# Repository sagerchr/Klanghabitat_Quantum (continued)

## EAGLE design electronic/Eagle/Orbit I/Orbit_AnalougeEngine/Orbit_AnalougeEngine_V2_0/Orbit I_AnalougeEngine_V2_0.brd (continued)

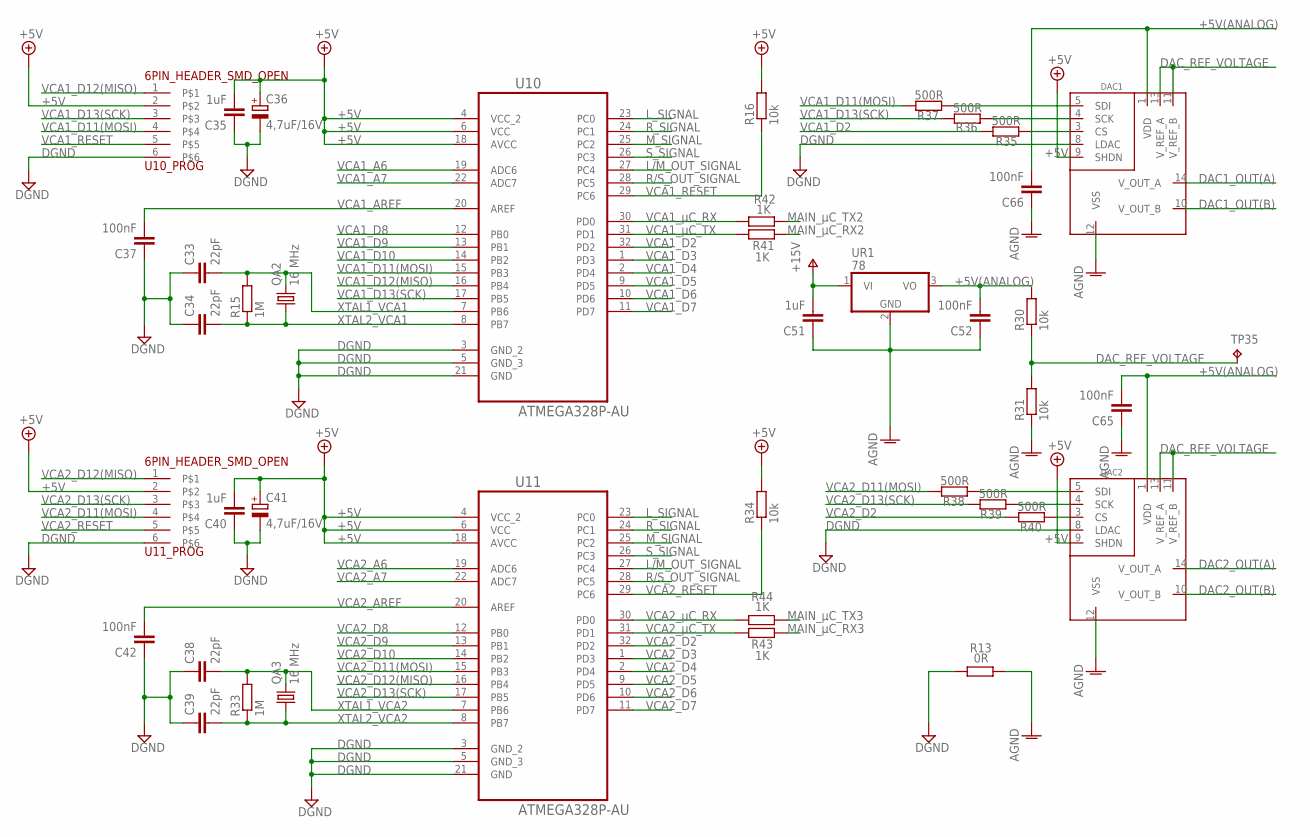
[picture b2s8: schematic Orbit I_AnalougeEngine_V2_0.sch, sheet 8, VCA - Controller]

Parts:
C33, C34, C38, C39: 22pF; C0603
C35, C40, C51: 1uF; C0603
C36, C41: 4,7uF/16V; 153CLV-0605
C37, C42, C52, C65, C66: 100nF; C0603
DAC1, DAC2: MCP4922; SOIC16
QA2, QA3: 16 MHz; SM49
R13: 0R; R0805
R15, R33: 1M; R0805
R16, R30, R31, R34: 10k; R0805
R35, R36, R37, R38, R39, R40: 500R; R0805
R41, R42, R43, R44: 1K; R0805
TP35: TPTHT; THT_PIN
U10, U11: ATMEGA328P-AU; QFP80P900X900X120-32N
U10_PROG, U11_PROG: 6PIN_HEADER_SMD_OPEN
UR1: 78; TO252

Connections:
+5V: C35.2, C36.+, C40.2, C41.+, DAC1.9 (SHDN), DAC2.9 (SHDN), R16.2, R34.2, U10.4 (VCC_2), U10.6 (VCC), U10.18 (AVCC), U10_PROG.2, U11.4 (VCC_2), U11.6 (VCC), U11.18 (AVCC), U11_PROG.2; also elsewhere on the board
+5V(ANALOG): C52.2, C65.2, C66.2, DAC1.1 (VDD), DAC2.1 (VDD), R30.2, UR1.3 (VO)
AGND: C51.1, C52.1, C65.1, C66.1, DAC1.12 (VSS), DAC2.12 (VSS), R13.2, R31.1, UR1.2 (GND); also elsewhere on the board
DAC1_OUT(A): DAC1.14 (V_OUT_A); also elsewhere on the board
DAC1_OUT(B): DAC1.10 (V_OUT_B); also elsewhere on the board
DAC2_OUT(A): DAC2.14 (V_OUT_A); also elsewhere on the board
DAC2_OUT(B): DAC2.10 (V_OUT_B); also elsewhere on the board
DAC_REF_VOLTAGE: DAC1.11 (V_REF_B), DAC1.13 (V_REF_A), DAC2.11 (V_REF_B), DAC2.13 (V_REF_A), R30.1, R31.2, TP35.P$1
DGND: C33.1, C34.1, C35.1, C36.-, C37.1, C38.1, C39.1, C40.1, C41.-, C42.1, DAC1.8 (LDAC), DAC2.8 (LDAC), R13.1, U10.3 (GND_2), U10.5 (GND_3), U10.21 (GND), U10_PROG.6, U11.3 (GND_2), U11.5 (GND_3), U11.21 (GND), U11_PROG.6; also elsewhere on the board
L/M_OUT_SIGNAL: U10.27 (PC4), U11.27 (PC4); also elsewhere on the board
L_SIGNAL: U10.23 (PC0), U11.23 (PC0); also elsewhere on the board
MAIN_µC_RX2: R41.2; also elsewhere on the board
MAIN_µC_RX3: R43.2; also elsewhere on the board
MAIN_µC_TX2: R42.2; also elsewhere on the board
MAIN_µC_TX3: R44.2; also elsewhere on the board
M_SIGNAL: U10.25 (PC2), U11.25 (PC2); also elsewhere on the board
unnamed: DAC1.3 (CS), R35.2
unnamed: DAC1.4 (SCK), R36.2
unnamed: DAC1.5 (SDI), R37.2
unnamed: DAC2.3 (CS), R40.2
unnamed: DAC2.4 (SCK), R39.2
unnamed: DAC2.5 (SDI), R38.2
R/S_OUT_SIGNAL: U10.28 (PC5), U11.28 (PC5); also elsewhere on the board
R_SIGNAL: U10.24 (PC1), U11.24 (PC1); also elsewhere on the board
S_SIGNAL: U10.26 (PC3), U11.26 (PC3); also elsewhere on the board
V+: C51.2, UR1.1 (VI); also elsewhere on the board
VCA1_A6: U10.19 (ADC6)
VCA1_A7: U10.22 (ADC7)
VCA1_AREF: C37.2, U10.20 (AREF)
VCA1_D2: R35.1, U10.32 (PD2)
VCA1_D3: U10.1 (PD3)
VCA1_D4: U10.2 (PD4)
VCA1_D5: U10.9 (PD5)
VCA1_D6: U10.10 (PD6)
VCA1_D7: U10.11 (PD7)
VCA1_D8: U10.12 (PB0)
VCA1_D9: U10.13 (PB1)
VCA1_D10: U10.14 (PB2)
VCA1_D11(MOSI): R37.1, U10.15 (PB3), U10_PROG.4
VCA1_D12(MISO): U10.16 (PB4), U10_PROG.1
VCA1_D13(SCK): R36.1, U10.17 (PB5), U10_PROG.3
VCA1_RESET: R16.1, U10.29 (PC6), U10_PROG.5
VCA1_µC_RX: R42.1, U10.30 (PD0)
VCA1_µC_TX: R41.1, U10.31 (PD1)
VCA2_A6: U11.19 (ADC6)
VCA2_A7: U11.22 (ADC7)
VCA2_AREF: C42.2, U11.20 (AREF)
VCA2_D2: R40.1, U11.32 (PD2)
VCA2_D3: U11.1 (PD3)
VCA2_D4: U11.2 (PD4)
VCA2_D5: U11.9 (PD5)
VCA2_D6: U11.10 (PD6)
VCA2_D7: U11.11 (PD7)
VCA2_D8: U11.12 (PB0)
VCA2_D9: U11.13 (PB1)
VCA2_D10: U11.14 (PB2)
VCA2_D11(MOSI): R38.1, U11.15 (PB3), U11_PROG.4
VCA2_D12(MISO): U11.16 (PB4), U11_PROG.1
VCA2_D13(SCK): R39.1, U11.17 (PB5), U11_PROG.3
VCA2_RESET: R34.1, U11.29 (PC6), U11_PROG.5
VCA2_µC_RX: R44.1, U11.30 (PD0)
VCA2_µC_TX: R43.1, U11.31 (PD1)
XTAL1_VCA1: C33.2, QA2.2, R15.2, U10.7 (PB6)
XTAL1_VCA2: C38.2, QA3.2, R33.2, U11.7 (PB6)
XTAL2_VCA1: C34.2, QA2.1, R15.1, U10.8 (PB7)
XTAL2_VCA2: C39.2, QA3.1, R33.1, U11.8 (PB7)

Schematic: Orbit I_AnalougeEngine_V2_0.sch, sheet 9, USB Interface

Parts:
C19, C32, C43: 100nF; C0603
C23, C24: 22pF; C0603
C31: 1uF; C0603
D1: Shotky-CD1206; SOD323-R
F1: FUSE_500 mA; RESETABLE-FUSE
Q1: BLM21; RESC2012X85
QA1: 16 MHz; SM49
R1, R2: 22R; R0805
R3, R4: 1M; R0805
R5, R6, R45: 1k; R0805
U5: ATMEGA16U2-AU; QFP80P900X900X120-32N
U5_PROG: 6PIN_HEADER_SMD_OPEN
USB1: SMARTPRJ_PN61729
V1, V2: CG0603ML; VARC2513X70

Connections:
+5V: C19.1, D1.C, R4.2, U5.4 (VCC), U5.32 (AVCC), U5_PROG.2; also elsewhere on the board
C_D(+): R2.1, USB1.3, V2.1
C_D(-): R1.1, USB1.2, V1.1
C_UVCC: F1.1, USB1.1
D(+): R2.2, U5.29 (D+)
D(-): R1.2, U5.30 (D-)
DGND: C19.2, C23.1, C24.1, C32.2, R45.1, U5.3 (GND), U5_PROG.6; also elsewhere on the board
MAIN_µC_RESET: C43.1; also elsewhere on the board
MAIN_µC_RX0: R5.2; also elsewhere on the board
MAIN_µC_TX0: R6.2; also elsewhere on the board
unnamed: Q1.1, USB1.P$1, USB1.P$2, V1.2, V2.2
unnamed: C43.2, R45.2, U5.13 (/_HWB_/_AIN6_/_T0_/_INT7)_PD7)
UCAP: C31.2, U5.27 (UCAP)
USB_µC_MISO: U5.17 (PB3_(PDO_/_MISO_/_PCINT3)), U5_PROG.1
USB_µC_MOSI: U5.16 ((PDI_/_MOSI_/_PCINT2)_PB2), U5_PROG.4
USB_µC_RESET: D1.A, R4.1, U5.24 (~RESET_(PC1_/_DW)), U5_PROG.5
USB_µC_RX: R6.1, U5.8 ((RXD1_/_AIN1_/_INT2)_PD2)
USB_µC_SCK: U5.15 ((SCLK_/_PCINT1)_PB1), U5_PROG.3
USB_µC_TX: R5.1, U5.9 ((TXD1_/_INT3)_PD3)
USB_µC_UGND: C31.1, Q1.2, U5.28 (UGND), USB1.4
USB_µC_XTAL1: C24.2, QA1.2, R3.2, U5.1 (XTAL1)
USB_µC_XTAL2: C23.2, QA1.1, R3.1, U5.2 ((PC0)_XTAL2)
UVCC: C32.1, F1.2, U5.31 (UVCC)

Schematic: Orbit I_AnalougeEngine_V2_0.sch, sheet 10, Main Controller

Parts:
C20, C47, C48, C49, C50: 100nF; C0603
C44, C45, C46: 22pF; C0603
CONN1: 10PIN_HEADER_SMD; 87832-10
D2: Shotky-CD1206; SOD323-R
QA4: 16 MHz; SM49
R32, R68: 1k; R0805
R46, R47: 1M; R0805
TP27, TP28, TP29, TP30, TP31, TP32, TP33, TP34: TPTHT; THT_PIN
U1: ATMEGA2560-16AU; QFP50P1600X1600X120-100N
U1_PROG: MAIN_µC; 6PIN_HEADER_SMD_OPEN

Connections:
+5V: C20.1, C47.1, C48.1, C49.1, CONN1.1, CONN1.2, CONN1.3, D2.C, R46.2, U1.10 (VCC_3), U1.31 (VCC_2), U1.61 (VCC_4), U1.80 (VCC), U1.100 (AVCC), U1_PROG.2; also elsewhere on the board
DGND: C20.2, C44.1, C45.1, C46.2, C47.2, C48.2, C49.2, C50.2, CONN1.5, CONN1.6, CONN1.7, CONN1.8, CONN1.10, U1.11 (GND_2), U1.32 (GND_4), U1.62 (GND_3), U1.81 (GND_5), U1.99 (GND), U1_PROG.6; also elsewhere on the board
L/M_OUT_SIGNAL: U1.93 (PF4_(ADC4/TCK)); also elsewhere on the board
L_SIGNAL: U1.97 (PF0_(ADC0)); also elsewhere on the board
MAIN_µC_AREF: C50.1, U1.98 (AREF)
MAIN_µC_D2: U1.6 ((OC3B/INT4)_PE4); also elsewhere on the board
MAIN_µC_D3: U1.7 ((OC3C/INT5)_PE5); also elsewhere on the board
MAIN_µC_D4: U1.1 ((OC0B)_PG5); also elsewhere on the board
MAIN_µC_D5: U1.5 ((OC3A/AIN1)_PE3); also elsewhere on the board
MAIN_µC_D6: U1.15 ((OC4A)_PH3); also elsewhere on the board
MAIN_µC_D7: U1.16 ((OC4B)_PH4); also elsewhere on the board
MAIN_µC_PB1(SCK): U1.20 ((SCK/PCINT1)_PB1), U1_PROG.3
MAIN_µC_PB2(MOSI): U1.21 ((MOSI/PCINT2)_PB2), U1_PROG.4
MAIN_µC_PB3(MISO): U1.22 ((MISO/PCINT3)_PB3), U1_PROG.1
MAIN_µC_RESET: C46.1, D2.A, R46.1, U1.30 (~RESET), U1_PROG.5; also elsewhere on the board
MAIN_µC_RX0: TP31.P$1, U1.2 ((RXD0/PCINT8)_PE0); also elsewhere on the board
MAIN_µC_RX1: R68.2, U1.45 ((RXD1/INT2)_PD2)
MAIN_µC_RX2: TP27.P$1, U1.12 ((RXD2)_PH0); also elsewhere on the board
MAIN_µC_RX3: TP33.P$1, U1.63 (PJ0_(RXD3/PCINT9)); also elsewhere on the board
MAIN_µC_TX0: TP32.P$1, U1.3 ((TXD0)_PE1); also elsewhere on the board
MAIN_µC_TX1: R32.2, U1.46 ((TXD1/INT3)_PD3)
MAIN_µC_TX2: TP28.P$1, U1.13 ((TXD2)_PH1); also elsewhere on the board
MAIN_µC_TX3: TP34.P$1, U1.64 (PJ1_(TXD3/PCINT10)); also elsewhere on the board
MAIN_µC_XTAL1: C44.2, QA4.2, R47.2, U1.34 (XTAL1)
MAIN_µC_XTAL2: C45.2, QA4.1, R47.1, U1.33 (XTAL2)
M_SIGNAL: U1.95 (PF2_(ADC2)); also elsewhere on the board
unnamed: CONN1.4, R68.1, TP29.P$1
unnamed: CONN1.9, R32.1, TP30.P$1
R/S_OUT_SIGNAL: U1.92 (PF5_(ADC5/TMS)); also elsewhere on the board
R_SIGNAL: U1.96 (PF1_(ADC1)); also elsewhere on the board
S_SIGNAL: U1.94 (PF3_(ADC3)); also elsewhere on the board
VCA1_EC+: U1.90 (PF7_(ADC7/TDI)); also elsewhere on the board
VCA2_EC+: U1.91 (PF6_(ADC6/TDO)); also elsewhere on the board

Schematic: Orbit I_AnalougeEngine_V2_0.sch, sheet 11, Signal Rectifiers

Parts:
C9, C10, C15, C16, C17, C18: 100nF; C0603
D3, D4, D5, D6, D7, D8, D9, D10, D11, D12, D13, D14: 4148; SOD323-R
IC2, IC3, IC6: OP275; SOIC8
L: 0R; R0805
L/M_OUT: 0R; R0805
M: 0R; R0805
R: 0R; R0805
R17, R18, R19, R20, R21, R22, R23, R24, R25, R26, R27, R28: 100k; R0805
R/S_OUT: 0R; R0805
S: 0R; R0805
TP01, TP02, TP03, TP04, TP05, TP06: TPTHT; THT_PIN

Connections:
AGND: C9.2, C10.2, C15.2, C16.2, C17.2, C18.2, IC2.3 (+IN), IC2.5 (+IN), IC3.3 (+IN), IC3.5 (+IN), IC6.3 (+IN), IC6.5 (+IN); also elsewhere on the board
L: R17.1; also elsewhere on the board
L/M_OUT(VCA1_OUT): R25.1; also elsewhere on the board
L/M_OUT_SIGNAL: L/M_OUT.2, TP03.P$1; also elsewhere on the board
L_SIGNAL: L.2, TP01.P$1; also elsewhere on the board
M: R21.1; also elsewhere on the board
M_SIGNAL: M.2, TP05.P$1; also elsewhere on the board
unnamed: D5.C, L.1, R18.2
unnamed: D4.A, IC2.2 (-IN), R17.2, R18.1
unnamed: D4.C, D5.A, IC2.1 (OUT)
unnamed: D6.A, IC2.6 (-IN), R19.2, R20.1
unnamed: D6.C, D7.A, IC2.7 (OUT)
unnamed: D7.C, R.1, R20.2
unnamed: D8.A, IC3.2 (-IN), R21.2, R22.1
unnamed: D8.C, D9.A, IC3.1 (OUT)
unnamed: D9.C, M.1, R22.2
unnamed: D10.A, IC3.6 (-IN), R23.2, R24.1
unnamed: D10.C, D11.A, IC3.7 (OUT)
unnamed: D11.C, R24.2, S.1
unnamed: D3.A, IC6.2 (-IN), R25.2, R26.1
unnamed: D3.C, D12.A, IC6.1 (OUT)
unnamed: D12.C, L/M_OUT.1, R26.2
unnamed: D13.A, IC6.6 (-IN), R27.2, R28.1
unnamed: D13.C, D14.A, IC6.7 (OUT)
unnamed: D14.C, R28.2, R/S_OUT.1
R: R19.1; also elsewhere on the board
R/S_OUT(VCA2_OUT): R27.1; also elsewhere on the board
R/S_OUT_SIGNAL: R/S_OUT.2, TP04.P$1; also elsewhere on the board
R_SIGNAL: R.2, TP02.P$1; also elsewhere on the board
S: R23.1; also elsewhere on the board
S_SIGNAL: S.2, TP06.P$1; also elsewhere on the board
V+: C10.1, C16.1, C18.1, IC2.8 (V+), IC3.8 (V+), IC6.8 (V+); also elsewhere on the board
V-: C9.1, C15.1, C17.1, IC2.4 (V-), IC3.4 (V-), IC6.4 (V-); also elsewhere on the board

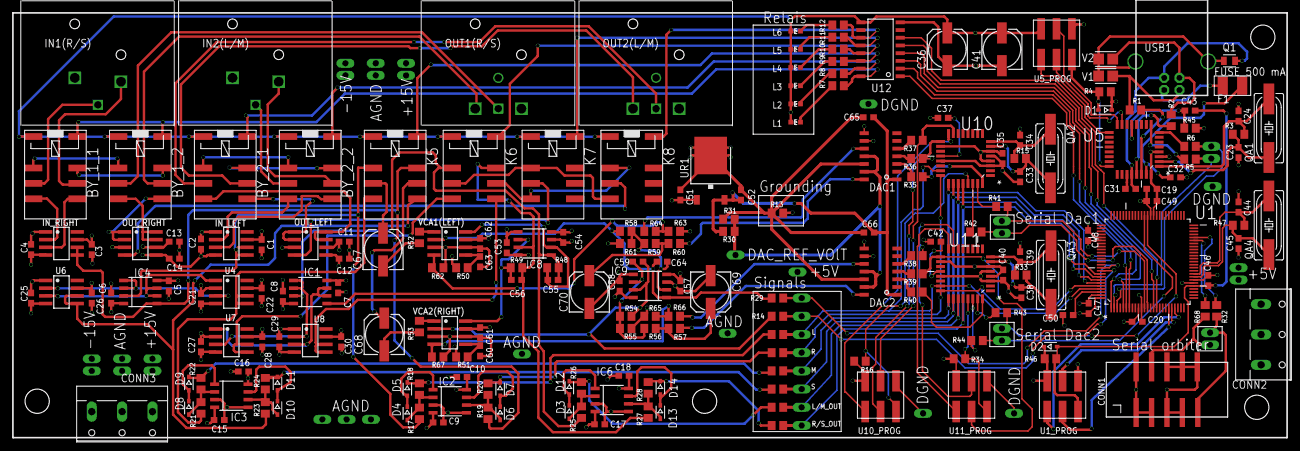
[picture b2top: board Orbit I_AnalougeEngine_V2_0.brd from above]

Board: 4 copper layers, 210.0 x 70.0 mm, 258 parts (0 on the bottom side), 170 nets.

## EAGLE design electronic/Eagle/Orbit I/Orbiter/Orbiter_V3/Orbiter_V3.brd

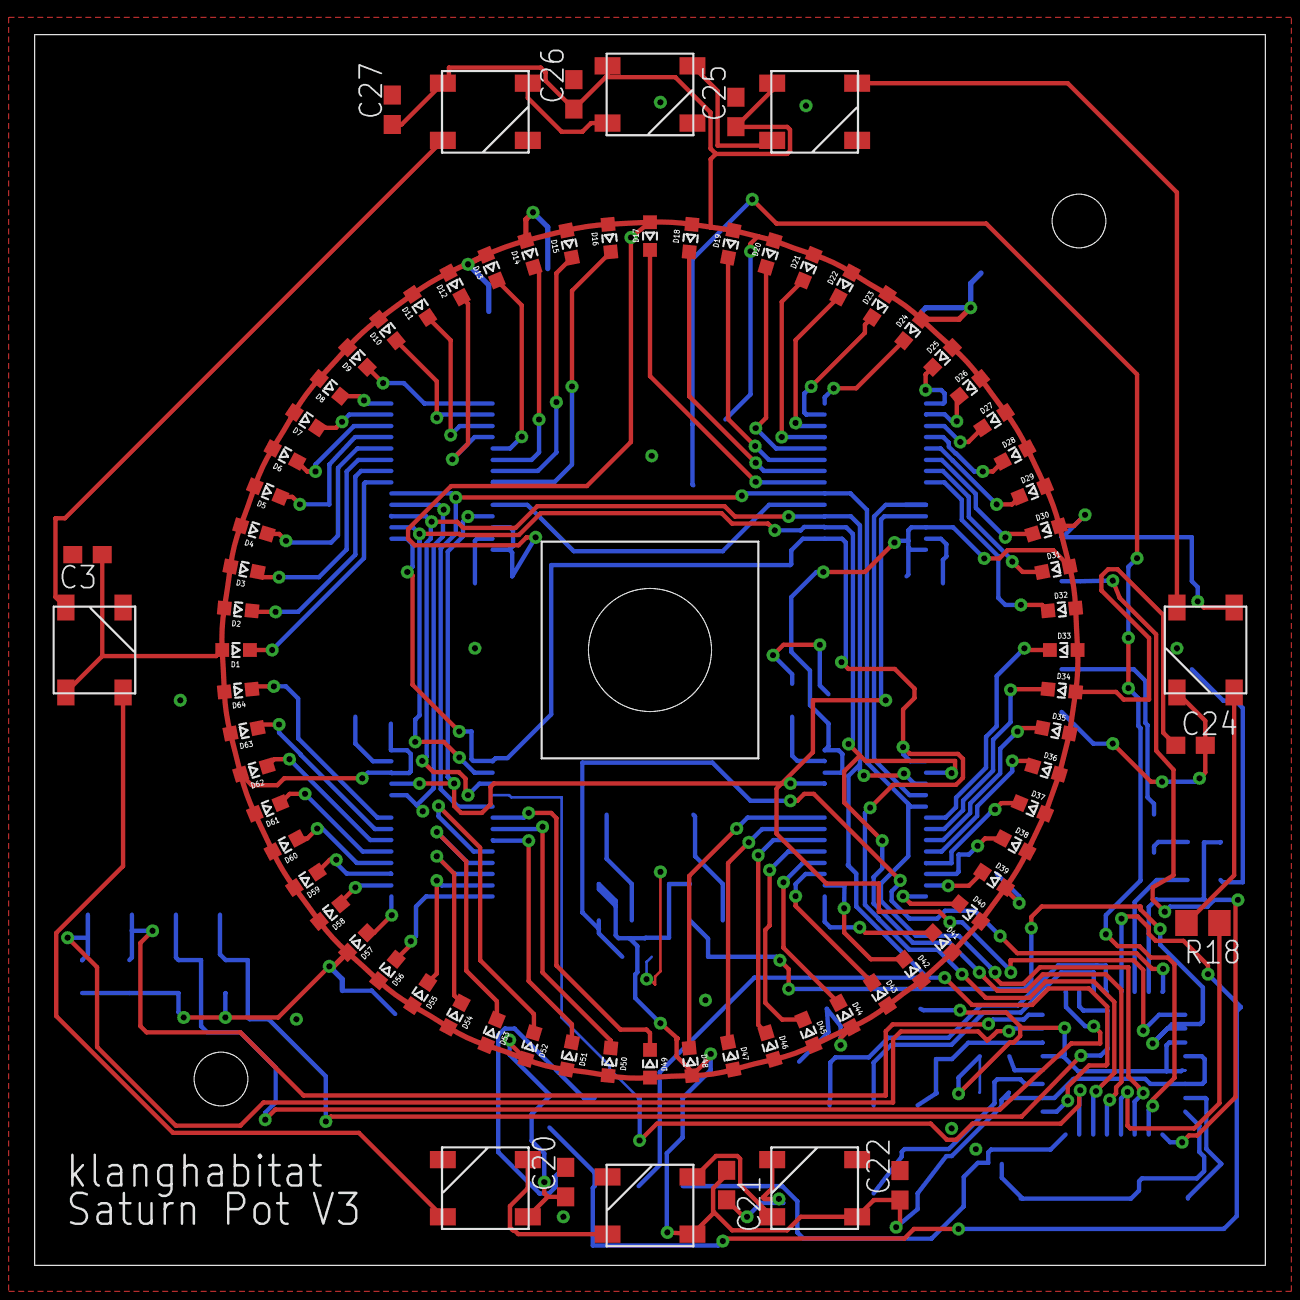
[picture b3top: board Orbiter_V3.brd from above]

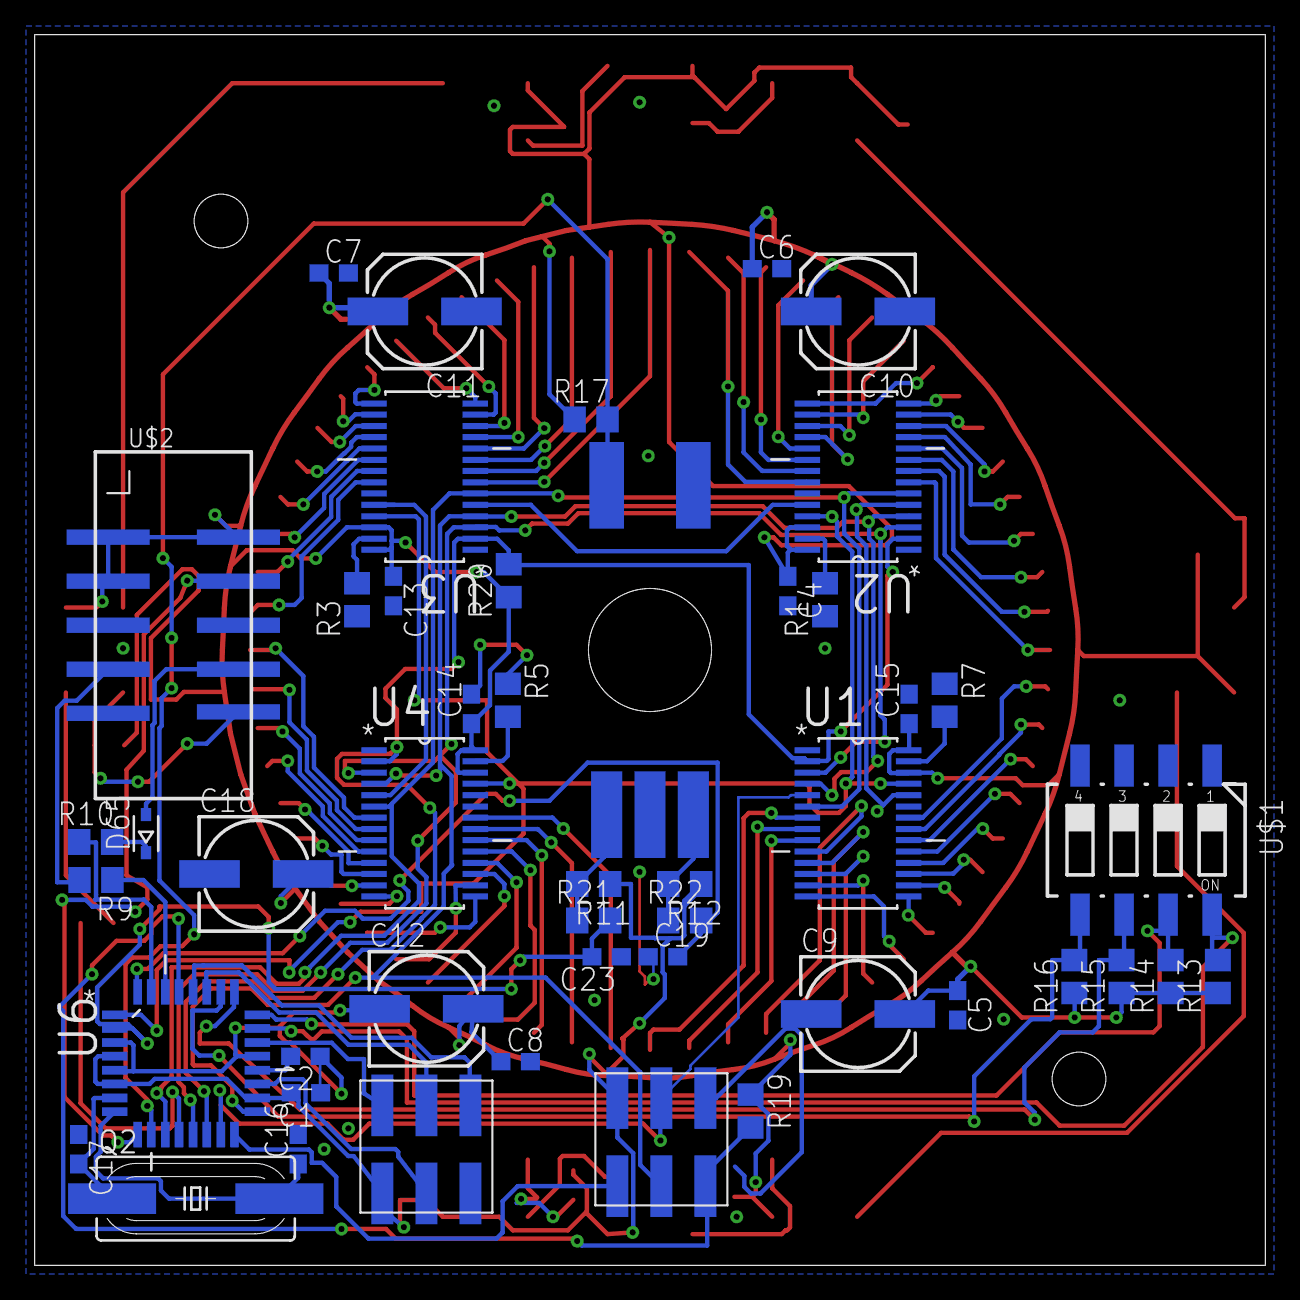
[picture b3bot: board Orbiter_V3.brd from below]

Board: 2 copper layers, 71.0 x 71.0 mm, 129 parts (47 on the bottom side), 112 nets.

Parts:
C1: 1uF; C0603
C2: 100nF; C0603
C3, C4, C5, C6, C7, C8, C13, C14, C15, C20, C21, C22, C24, C25, C26, C27: 100n; C0603
C9, C10, C11, C12: 10u; 153CLV-0605
C16, C17: 22p; C0603
C18: 4,7uF/16V; 153CLV-0605
C19, C23: 10nF; C0603
D1, D2, D3, D4, D5, D6, D7, D8, D9, D10, D11, D12, D13, D14, D15, D16, D17, D18, D19, D20, D21, D22, D23, D24, D25, D26, D27, D28, D29, D30, D31, D32, D33, D34, D35, D36, D37, D38, D39, D40, D41, D42, D43, D44, D45, D46, D47, D48, D49, D50, D51, D52, D53, D54, D55, D56, D57, D58, D59, D60, D61, D62, D63, D64: SMD_LED_0603; WL-SMCW_0603
D65: 4148; SOD323-R
Q2: 16MHZ; SM49
R1, R3, R5, R7: 2k; R0805
R9, R10, R18: 1k; R0805
R11, R12, R13, R14, R15, R16, R17, R19, R20, R21, R22: 10k; R0805
U1, U2, U3, U4: TLC5940; SOP65P640X120-29N
U6: ATMEGA328; QFP80P900X900X120-32N
U$1: 4PIN_DIP; CTS-219-04
U$2: 10PIN_HEADER_SMD; 87832-10
U$3, U$5: 6PIN_HEADER_SMD_OPEN
U$4: BOURNS_ENCODER; BOURNS_ENCODER_SMD
WS2, WS3, WS4, WS5, WS6, WS8, WS9, WS10: WS2812

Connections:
A0: R13.2, U6.23, U$1.8
A1: R14.2, U6.24, U$1.7
A2: R15.2, U6.25, U$1.6
A3: R16.2, U6.26, U$1.5
A4: U6.27, U$5.4
A5: U6.28, U$5.6
A6: U6.19, U$5.3
A7: U6.22, U$5.2
D0/RX: R9.1, U6.30
D1/TX: R10.1, U6.31
D2/TB: C19.2, R22.2, U6.32
D3/GSCLK: U1.25, U2.25, U3.25, U4.25, U6.1
D4/TA: C23.2, R21.2, U6.2
D5: U6.9, U$2.4
D6/SWITCH: R17.2, U6.10, U$4.S2
D7/MODE: U1.6, U2.6, U3.6, U4.6, U6.11
D8/WS2812: R18.1, U6.12
D9/XLAT: U1.3, U2.3, U3.3, U4.3, U6.13
D10/BLANK: R20.2, U1.2, U2.2, U3.2, U4.2, U6.14
D11/MOSI/SIN: U1.5, U6.15, U$3.4
D12/MISO: U6.16, U$3.1
D13/SCK: U1.4, U2.4, U3.4, U4.4, U6.17, U$3.3
GND: C1.1, C2.1, C3.2, C4.2, C5.2, C6.2, C7.2, C8.2, C9.-, C10.-, C11.-, C12.-, C13.2, C14.2, C15.2, C16.2, C17.1, C18.-, C19.1, C20.2, C21.2, C22.2, C23.1, C24.2, C25.2, C26.2, C27.2, R1.1, R3.1, R5.1, R7.1, U1.1, U2.1, U3.1, U4.1, U6.3, U6.5, U6.21, U$1.1, U$1.2, U$1.3, U$1.4, U$2.5, U$2.6, U$2.9, U$2.10, U$3.6, U$4.S1, U$4.VDC, U$5.5, WS2.GND, WS3.GND, WS4.GND, WS5.GND, WS6.GND, WS8.GND, WS9.GND, WS10.GND
IREF_U1: R1.2, U2.27
IREF_U2: R3.2, U3.27
IREF_U3: R5.2, U4.27
IREF_U4: R7.2, U1.27
unnamed: D1.1, U2.7
unnamed: U1.24, U2.5
unnamed: D2.1, U2.8
unnamed: D8.1, U2.14
unnamed: D3.1, U2.9
unnamed: D9.1, U2.15
unnamed: D4.1, U2.10
unnamed: D10.1, U2.16
unnamed: D5.1, U2.11
unnamed: D6.1, U2.12
unnamed: D7.1, U2.13
unnamed: D11.1, U2.17
unnamed: D12.1, U2.18
unnamed: D13.1, U2.19
unnamed: D14.1, U2.20
unnamed: D15.1, U2.21
unnamed: D16.1, U2.22
unnamed: D17.1, U3.7
unnamed: D18.1, U3.8
unnamed: D19.1, U3.9
unnamed: D20.1, U3.10
unnamed: D21.1, U3.11
unnamed: D22.1, U3.12
unnamed: D23.1, U3.13
unnamed: D24.1, U3.14
unnamed: D25.1, U3.15
unnamed: D26.1, U3.16
unnamed: D27.1, U3.17
unnamed: D28.1, U3.18
unnamed: D29.1, U3.19
unnamed: D30.1, U3.20
unnamed: D31.1, U3.21
unnamed: D32.1, U3.22
unnamed: D33.1, U4.7
unnamed: D34.1, U4.8
unnamed: D35.1, U4.9
unnamed: D36.1, U4.10
unnamed: D37.1, U4.11
unnamed: D38.1, U4.12
unnamed: D39.1, U4.13
unnamed: D40.1, U4.14
unnamed: D41.1, U4.15
unnamed: D42.1, U4.16
unnamed: D43.1, U4.17
unnamed: D44.1, U4.18
unnamed: D45.1, U4.19
unnamed: D46.1, U4.20
unnamed: D47.1, U4.21
unnamed: D48.1, U4.22
unnamed: D49.1, U1.7
unnamed: D50.1, U1.8
unnamed: D51.1, U1.9
unnamed: D52.1, U1.10
unnamed: D53.1, U1.11
unnamed: D54.1, U1.12
unnamed: D55.1, U1.13
unnamed: D56.1, U1.14
unnamed: D57.1, U1.15
unnamed: D58.1, U1.16
unnamed: D59.1, U1.17
unnamed: D60.1, U1.18
unnamed: D61.1, U1.19
unnamed: D62.1, U1.20
unnamed: D63.1, U1.21
unnamed: D64.1, U1.22
unnamed: R18.2, WS2.DIN
unnamed: D65.C, R10.2
unnamed: WS2.DOUT, WS3.DIN
unnamed: WS3.DOUT, WS4.DIN
unnamed: C17.2, Q2.1, U6.7
unnamed: C16.1, Q2.2, U6.8
unnamed: WS4.DOUT, WS5.DIN
unnamed: WS5.DOUT, WS6.DIN
unnamed: WS6.DOUT, WS8.DIN
unnamed: WS8.DOUT, WS9.DIN
unnamed: WS9.DOUT, WS10.DIN
unnamed: C2.2, U6.20
RESET: R19.2, U6.29, U$3.5
RX: R9.2, U$2.7
SIN_U2: U2.24, U3.5
SIN_U3: U3.24, U4.5
TA: R11.2, R21.1, U$4.TA
TB: R12.2, R22.1, U$4.TB
TX: D65.A, U$2.8
VCC: C1.2, C3.1, C4.1, C5.1, C6.1, C7.1, C8.1, C9.+, C10.+, C11.+, C12.+, C13.1, C14.1, C15.1, C18.+, C20.1, C21.1, C22.1, C24.1, C25.1, C26.1, C27.1, D1.2, D2.2, D3.2, D4.2, D5.2, D6.2, D7.2, D8.2, D9.2, D10.2, D11.2, D12.2, D13.2, D14.2, D15.2, D16.2, D17.2, D18.2, D19.2, D20.2, D21.2, D22.2, D23.2, D24.2, D25.2, D26.2, D27.2, D28.2, D29.2, D30.2, D31.2, D32.2, D33.2, D34.2, D35.2, D36.2, D37.2, D38.2, D39.2, D40.2, D41.2, D42.2, D43.2, D44.2, D45.2, D46.2, D47.2, D48.2, D49.2, D50.2, D51.2, D52.2, D53.2, D54.2, D55.2, D56.2, D57.2, D58.2, D59.2, D60.2, D61.2, D62.2, D63.2, D64.2, R11.1, R12.1, R13.1, R14.1, R15.1, R16.1, R17.1, R19.1, R20.1, U1.26, U1.28, U2.26, U2.28, U3.26, U3.28, U4.26, U4.28, U6.4, U6.6, U6.18, U$2.1, U$2.2, U$2.3, U$3.2, U$5.1, WS2.VDD, WS3.VDD, WS4.VDD, WS5.VDD, WS6.VDD, WS8.VDD, WS9.VDD, WS10.VDD

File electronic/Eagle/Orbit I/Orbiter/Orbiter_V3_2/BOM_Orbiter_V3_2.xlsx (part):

| ID: | BOM_Orbiter_V3_2 |  | date: | 12.03.2018
 | author: | Christian Sager
 | Part | Value | Device | Package | Digikey | Description | assemble
1 | A4 | TPSMD | TPSMD | TP | *** | Testpoint | no
2 | A5 | TPSMD | TPSMD | TP | *** | Testpoint | no
3 | C1 | 1uF | CAPACITOR";C0603" | 0603 | CC0805KKX7R7BB105 | condensor | yes
4 | C2 | 100n | CAPACITOR";C0603" | 0603 | C0603C104Z3VACTU | condensor | yes
5 | C4 | 100n | CAPACITOR";C0603" | 0603 | C0603C104Z3VACTU | condensor | yes
6 | C5 | 100n | CAPACITOR";C0603" | 0603 | C0603C104Z3VACTU | condensor | yes
7 | C6 | 100n | CAPACITOR";C0603" | 0603 | C0603C104Z3VACTU | condensor | yes
8 | C7 | 100n | CAPACITOR";C0603" | 0603 | C0603C104Z3VACTU | condensor | yes
9 | C8 | 100n | CAPACITOR";C0603" | 0603 | C0603C104Z3VACTU | condensor | yes
10 | C9 | 10u/50V | SMD_ELCTROLYTIC | 153CLV-0605 | 865080642006 | SMD Elektrolyt Kondensator 153CLV-0605 | yes
11 | C10 | 10u/50V | SMD_ELCTROLYTIC | 153CLV-0605 | 865080642006 | SMD Elektrolyt Kondensator 153CLV-0605 | yes
12 | C11 | 10u/50V | SMD_ELCTROLYTIC | 153CLV-0605 | 865080642006 | SMD Elektrolyt Kondensator 153CLV-0605 | yes
13 | C12 | 10u/50V | SMD_ELCTROLYTIC | 153CLV-0605 | 865080642006 | SMD Elektrolyt Kondensator 153CLV-0605 | yes
14 | C13 | 100n | CAPACITOR";C0603" | 0603 | C0603C104Z3VACTU | condensor | yes
15 | C14 | 100n | CAPACITOR";C0603" | 0603 | C0603C104Z3VACTU | condensor | yes
16 | C15 | 100n | CAPACITOR";C0603" | 0603 | C0603C104Z3VACTU | condensor | yes
17 | C16 | 22p | CAPACITOR";C0603" | 0603 | 06035A220JAT2A | condensor | yes
18 | C17 | 22p | CAPACITOR";C0603" | 0603 | 06035A220JAT2A | condensor | yes
19 | C18 | 4,7uF/16V | SMD_ELCTROLYTIC | 153CLV-0605 | 865060642004 | SMD Elektrolyt Kondensator 153CLV-0605 | yes
20 | C19 | 10nF | CAPACITOR";C0603" | 0603 | GRM188R71H103JA01D | condensor | yes
21 | C23 | 10nF | CAPACITOR";C0603" | 0603 | GRM188R71H103JA01D | condensor | yes
22 | CONECTOR | 10PIN_HEADER_SMD | 10PIN_HEADER_SMD | 87832-10 | 3020-10-0300-00 | 10 Pin Header (Flachbandkabel) | yes
23 | D1 | SMD_LED_0603 | SMD_LED_0603 | WL-SMCW_0603 | QBLP601-IW | SMD LED 0603 | yes
24 | D2 | SMD_LED_0603 | SMD_LED_0603 | WL-SMCW_0603 | QBLP601-IW | SMD LED 0603 | yes
25 | D3 | SMD_LED_0603 | SMD_LED_0603 | WL-SMCW_0603 | QBLP601-IW | SMD LED 0603 | yes
26 | D4 | SMD_LED_0603 | SMD_LED_0603 | WL-SMCW_0603 | QBLP601-IW | SMD LED 0603 | yes
27 | D5 | SMD_LED_0603 | SMD_LED_0603 | WL-SMCW_0603 | QBLP601-IW | SMD LED 0603 | yes
28 | D6 | SMD_LED_0603 | SMD_LED_0603 | WL-SMCW_0603 | QBLP601-IW | SMD LED 0603 | yes
29 | D7 | SMD_LED_0603 | SMD_LED_0603 | WL-SMCW_0603 | QBLP601-IW | SMD LED 0603 | yes
30 | D8 | SMD_LED_0603 | SMD_LED_0603 | WL-SMCW_0603 | QBLP601-IW | SMD LED 0603 | yes
31 | D9 | SMD_LED_0603 | SMD_LED_0603 | WL-SMCW_0603 | QBLP601-IW | SMD LED 0603 | yes
32 | D10 | SMD_LED_0603 | SMD_LED_0603 | WL-SMCW_0603 | QBLP601-IW | SMD LED 0603 | yes
33 | D11 | SMD_LED_0603 | SMD_LED_0603 | WL-SMCW_0603 | QBLP601-IW | SMD LED 0603 | yes
34 | D12 | SMD_LED_0603 | SMD_LED_0603 | WL-SMCW_0603 | QBLP601-IW | SMD LED 0603 | yes
35 | D13 | SMD_LED_0603 | SMD_LED_0603 | WL-SMCW_0603 | QBLP601-IW | SMD LED 0603 | yes
36 | D14 | SMD_LED_0603 | SMD_LED_0603 | WL-SMCW_0603 | QBLP601-IW | SMD LED 0603 | yes
37 | D15 | SMD_LED_0603 | SMD_LED_0603 | WL-SMCW_0603 | QBLP601-IW | SMD LED 0603 | yes
38 | D16 | SMD_LED_0603 | SMD_LED_0603 | WL-SMCW_0603 | QBLP601-IW | SMD LED 0603 | yes
39 | D17 | SMD_LED_0603 | SMD_LED_0603 | WL-SMCW_0603 | QBLP601-IW | SMD LED 0603 | yes
40 | D18 | SMD_LED_0603 | SMD_LED_0603 | WL-SMCW_0603 | QBLP601-IW | SMD LED 0603 | yes
41 | D19 | SMD_LED_0603 | SMD_LED_0603 | WL-SMCW_0603 | QBLP601-IW | SMD LED 0603 | yes
42 | D20 | SMD_LED_0603 | SMD_LED_0603 | WL-SMCW_0603 | QBLP601-IW | SMD LED 0603 | yes
43 | D21 | SMD_LED_0603 | SMD_LED_0603 | WL-SMCW_0603 | QBLP601-IW | SMD LED 0603 | yes
44 | D22 | SMD_LED_0603 | SMD_LED_0603 | WL-SMCW_0603 | QBLP601-IW | SMD LED 0603 | yes
45 | D23 | SMD_LED_0603 | SMD_LED_0603 | WL-SMCW_0603 | QBLP601-IW | SMD LED 0603 | yes
46 | D24 | SMD_LED_0603 | SMD_LED_0603 | WL-SMCW_0603 | QBLP601-IW | SMD LED 0603 | yes
47 | D25 | SMD_LED_0603 | SMD_LED_0603 | WL-SMCW_0603 | QBLP601-IW | SMD LED 0603 | yes
48 | D26 | SMD_LED_0603 | SMD_LED_0603 | WL-SMCW_0603 | QBLP601-IW | SMD LED 0603 | yes
49 | D27 | SMD_LED_0603 | SMD_LED_0603 | WL-SMCW_0603 | QBLP601-IW | SMD LED 0603 | yes
50 | D28 | SMD_LED_0603 | SMD_LED_0603 | WL-SMCW_0603 | QBLP601-IW | SMD LED 0603 | yes
51 | D29 | SMD_LED_0603 | SMD_LED_0603 | WL-SMCW_0603 | QBLP601-IW | SMD LED 0603 | yes
52 | D30 | SMD_LED_0603 | SMD_LED_0603 | WL-SMCW_0603 | QBLP601-IW | SMD LED 0603 | yes
53 | D31 | SMD_LED_0603 | SMD_LED_0603 | WL-SMCW_0603 | QBLP601-IW | SMD LED 0603 | yes
54 | D32 | SMD_LED_0603 | SMD_LED_0603 | WL-SMCW_0603 | QBLP601-IW | SMD LED 0603 | yes
55 | D33 | SMD_LED_0603 | SMD_LED_0603 | WL-SMCW_0603 | QBLP601-IW | SMD LED 0603 | yes
56 | D34 | SMD_LED_0603 | SMD_LED_0603 | WL-SMCW_0603 | QBLP601-IW | SMD LED 0603 | yes
57 | D35 | SMD_LED_0603 | SMD_LED_0603 | WL-SMCW_0603 | QBLP601-IW | SMD LED 0603 | yes
58 | D36 | SMD_LED_0603 | SMD_LED_0603 | WL-SMCW_0603 | QBLP601-IW | SMD LED 0603 | yes
59 | D37 | SMD_LED_0603 | SMD_LED_0603 | WL-SMCW_0603 | QBLP601-IW | SMD LED 0603 | yes
60 | D38 | SMD_LED_0603 | SMD_LED_0603 | WL-SMCW_0603 | QBLP601-IW | SMD LED 0603 | yes
61 | D39 | SMD_LED_0603 | SMD_LED_0603 | WL-SMCW_0603 | QBLP601-IW | SMD LED 0603 | yes
62 | D40 | SMD_LED_0603 | SMD_LED_0603 | WL-SMCW_0603 | QBLP601-IW | SMD LED 0603 | yes
63 | D41 | SMD_LED_0603 | SMD_LED_0603 | WL-SMCW_0603 | QBLP601-IW | SMD LED 0603 | yes
64 | D42 | SMD_LED_0603 | SMD_LED_0603 | WL-SMCW_0603 | QBLP601-IW | SMD LED 0603 | yes
65 | D43 | SMD_LED_0603 | SMD_LED_0603 | WL-SMCW_0603 | QBLP601-IW | SMD LED 0603 | yes
66 | D44 | SMD_LED_0603 | SMD_LED_0603 | WL-SMCW_0603 | QBLP601-IW | SMD LED 0603 | yes
67 | D45 | SMD_LED_0603 | SMD_LED_0603 | WL-SMCW_0603 | QBLP601-IW | SMD LED 0603 | yes
68 | D46 | SMD_LED_0603 | SMD_LED_0603 | WL-SMCW_0603 | QBLP601-IW | SMD LED 0603 | yes
69 | D47 | SMD_LED_0603 | SMD_LED_0603 | WL-SMCW_0603 | QBLP601-IW | SMD LED 0603 | yes
70 | D48 | SMD_LED_0603 | SMD_LED_0603 | WL-SMCW_0603 | QBLP601-IW | SMD LED 0603 | yes
71 | D49 | SMD_LED_0603 | SMD_LED_0603 | WL-SMCW_0603 | QBLP601-IW | SMD LED 0603 | yes
72 | D50 | SMD_LED_0603 | SMD_LED_0603 | WL-SMCW_0603 | QBLP601-IW | SMD LED 0603 | yes
73 | D51 | SMD_LED_0603 | SMD_LED_0603 | WL-SMCW_0603 | QBLP601-IW | SMD LED 0603 | yes
74 | D52 | SMD_LED_0603 | SMD_LED_0603 | WL-SMCW_0603 | QBLP601-IW | SMD LED 0603 | yes
75 | D53 | SMD_LED_0603 | SMD_LED_0603 | WL-SMCW_0603 | QBLP601-IW | SMD LED 0603 | yes
76 | D54 | SMD_LED_0603 | SMD_LED_0603 | WL-SMCW_0603 | QBLP601-IW | SMD LED 0603 | yes
77 | D55 | SMD_LED_0603 | SMD_LED_0603 | WL-SMCW_0603 | QBLP601-IW | SMD LED 0603 | yes
78 | D56 | SMD_LED_0603 | SMD_LED_0603 | WL-SMCW_0603 | QBLP601-IW | SMD LED 0603 | yes
79 | D57 | SMD_LED_0603 | SMD_LED_0603 | WL-SMCW_0603 | QBLP601-IW | SMD LED 0603 | yes
80 | D58 | SMD_LED_0603 | SMD_LED_0603 | WL-SMCW_0603 | QBLP601-IW | SMD LED 0603 | yes
81 | D59 | SMD_LED_0603 | SMD_LED_0603 | WL-SMCW_0603 | QBLP601-IW | SMD LED 0603 | yes
82 | D60 | SMD_LED_0603 | SMD_LED_0603 | WL-SMCW_0603 | QBLP601-IW | SMD LED 0603 | yes
83 | D61 | SMD_LED_0603 | SMD_LED_0603 | WL-SMCW_0603 | QBLP601-IW | SMD LED 0603 | yes
84 | D62 | SMD_LED_0603 | SMD_LED_0603 | WL-SMCW_0603 | QBLP601-IW | SMD LED 0603 | yes
85 | D63 | SMD_LED_0603 | SMD_LED_0603 | WL-SMCW_0603 | QBLP601-IW | SMD LED 0603 | yes
86 | D64 | SMD_LED_0603 | SMD_LED_0603 | WL-SMCW_0603 | QBLP601-IW | SMD LED 0603 | yes
87 | D65 | 4148 | 4148 | SOD323-R | 1N4148WSTR | Standard 4148 Diode SOD323 Format | yes
88 | DIP | 4PIN_DIP | 4PIN_DIP | CTS-219-04 | 219-4MST | 4 Bit DipSwitch | yes
89 | ENC. | BOURNS_ENCODER | BOURNS_ENCODER | BOURNS_ENCODER_SMD | PEC11R-4015K-S0024 | Bourns Rotay Encoder | no
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
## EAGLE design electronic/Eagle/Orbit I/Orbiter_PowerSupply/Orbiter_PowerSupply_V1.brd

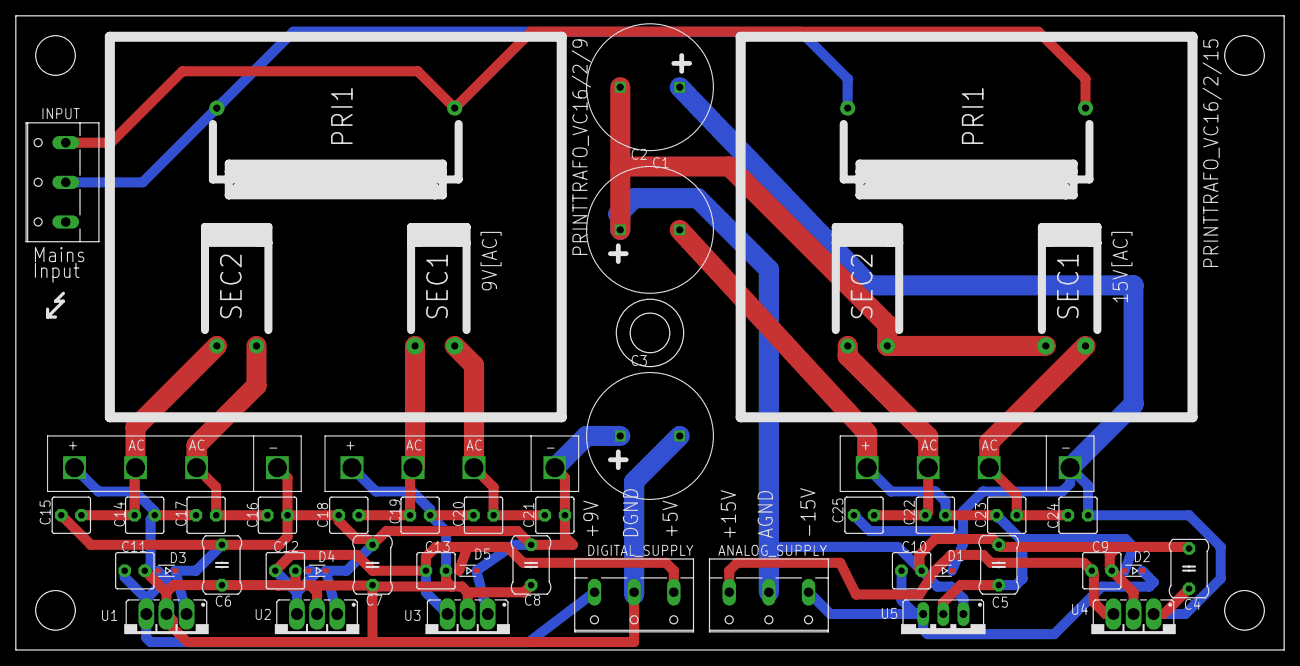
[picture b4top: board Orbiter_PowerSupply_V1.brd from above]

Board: 2 copper layers, 160.0 x 80.0 mm, 43 parts (0 on the bottom side), 17 nets.

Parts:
9V[AC]: PRINTTRAFO_VC16/2/9; PRINTTRAFO_VC16/2/...
15V[AC]: PRINTTRAFO_VC16/2/15; PRINTTRAFO_VC16/2/...
ANALOG_SUPPLY: Analog_Supply; W237-103
C1, C2, C3: 4700µF; ELECTROLYTIC_16MM
C4, C5, C6, C7, C8: 0,3 µF; C5MM
C9, C10, C11, C12, C13: 100nF; C2.5MM
C14, C15, C16, C17, C18, C19, C20, C21, C22, C23, C24, C25: 10nF; C2.5MM
D1, D2, D3, D4, D5: 4148_SOD323; SOD323-R
DIGITAL_SUPPLY: Digital_Supply; W237-103
INPUT: Mains Supply; W237-103
U1: 7809; 78XXS_
U2, U3: 7805; 78XXS_
U4: 7815; 78XXS_
U5: 7915; 79XXS
U$1, U$2, U$3: GLEICHRICHTER; SIL_RECTIFER

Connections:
5V: C12.1, C13.1, D4.A, D5.A, DIGITAL_SUPPLY.1, U2.OUT, U3.OUT
9V: C11.1, D3.A, DIGITAL_SUPPLY.3, U1.OUT
+15V: ANALOG_SUPPLY.3, C9.1, D1.A, U4.OUT
-15V: ANALOG_SUPPLY.1, C10.2, D2.C, U5.OUT
A_GND: 15V[AC].SEC1(-), 15V[AC].SEC2(+), ANALOG_SUPPLY.2, C1.-, C2.+, C4.2, C5.1, C9.2, C10.1, U4.GND, U5.GND
DIGITAL_GND: C3.-, C6.2, C7.2, C8.2, C11.2, C12.2, C13.2, C14.2, C17.2, C19.2, C20.2, DIGITAL_SUPPLY.2, U1.GND, U2.GND, U3.GND, U$2.-, U$3.-
unnamed: 9V[AC].PRI(+), 15V[AC].PRI(+), INPUT.3
unnamed: 9V[AC].PRI(-), 15V[AC].PRI(-), INPUT.2
unnamed: 15V[AC].SEC1(+), C23.1, C24.2, U$1.AC1
unnamed: 15V[AC].SEC2(-), C22.1, C25.2, U$1.AC2
unnamed: 9V[AC].SEC1(-), C18.2, C19.1, U$2.AC2
unnamed: 9V[AC].SEC1(+), C20.1, C21.2, U$2.AC1
unnamed: 9V[AC].SEC2(+), C16.2, C17.1, U$3.AC1
unnamed: 9V[AC].SEC2(-), C14.1, C15.2, U$3.AC2
unnamed: C2.-, C5.2, C22.2, C23.2, D2.A, U5.IN, U$1.-
unnamed: C1.+, C4.1, C24.1, C25.1, D1.C, U4.IN, U$1.+
unnamed: C3.+, C6.1, C7.1, C8.1, C15.1, C16.1, C18.1, C21.1, D3.C, D4.C, D5.C, U1.IN, U2.IN, U3.IN, U$2.+, U$3.+

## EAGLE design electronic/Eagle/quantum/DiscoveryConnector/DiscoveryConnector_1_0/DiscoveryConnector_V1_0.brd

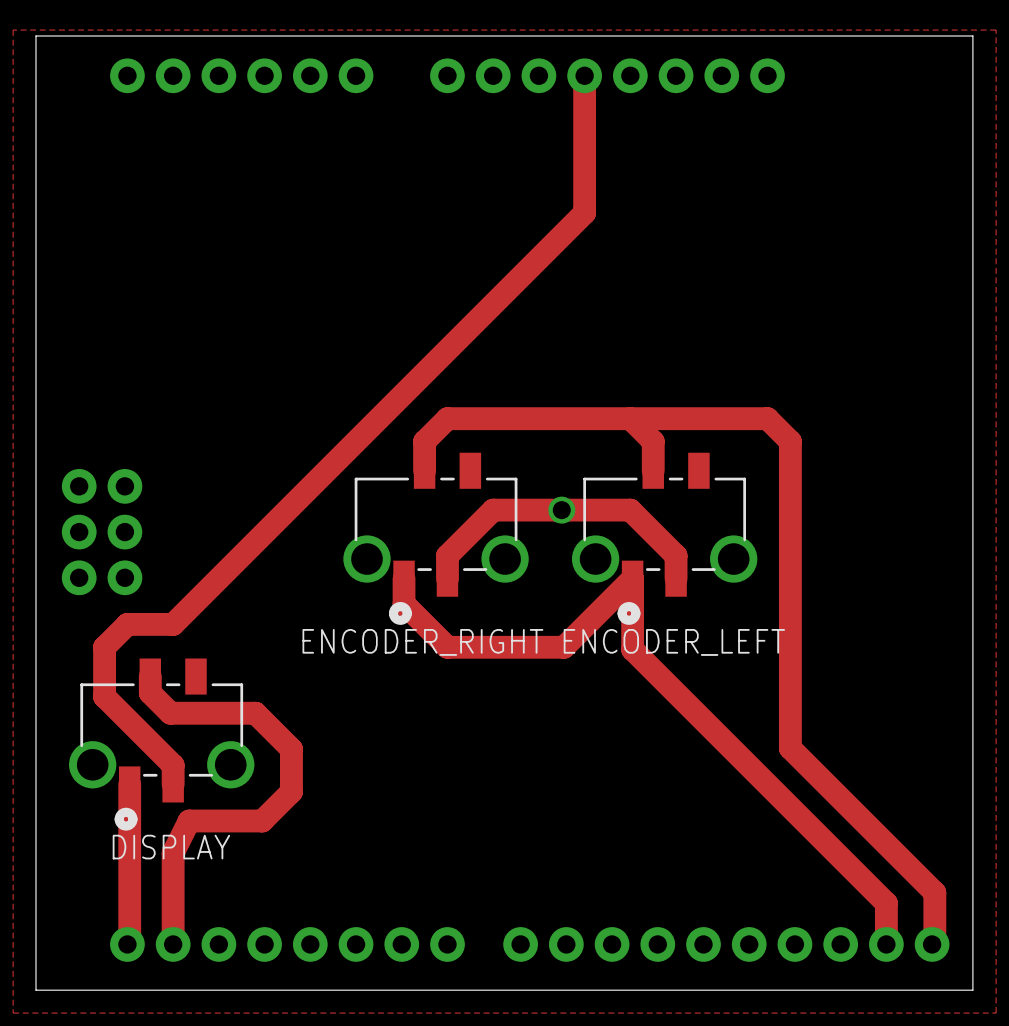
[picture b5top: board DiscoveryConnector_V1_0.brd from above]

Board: 2 copper layers, 52.0 x 53.0 mm, 4 parts (0 on the bottom side), 7 nets.

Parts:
B1: ARDUINO_UNO_R3; ARDUINO_R3
DISPLAY: 90814-0204; MOLEX_90814-0204
ENCODER_LEFT: 90814-0204; MOLEX_90814-0204
ENCODER_RIGHT: 90814-0204; MOLEX_90814-0204

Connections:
3V3: B1.3.3V, ENCODER_LEFT.3, ENCODER_RIGHT.3
GND: B1.GND@1, B1.GND@2, B1.GND@3, B1.GND@4, DISPLAY.4, ENCODER_LEFT.4, ENCODER_RIGHT.4
unnamed: B1.5V, DISPLAY.3
SCL: B1.SCL, ENCODER_LEFT.2, ENCODER_RIGHT.2
SDA: B1.SDA, ENCODER_LEFT.1, ENCODER_RIGHT.1
USART6_RX: B1.D1, DISPLAY.2
USART6_TX: B1.D0, DISPLAY.1
